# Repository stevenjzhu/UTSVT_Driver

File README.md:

# UTSVT_Driver
This is a PCB board to interface the motors and various components through CAN bus for UTSVT

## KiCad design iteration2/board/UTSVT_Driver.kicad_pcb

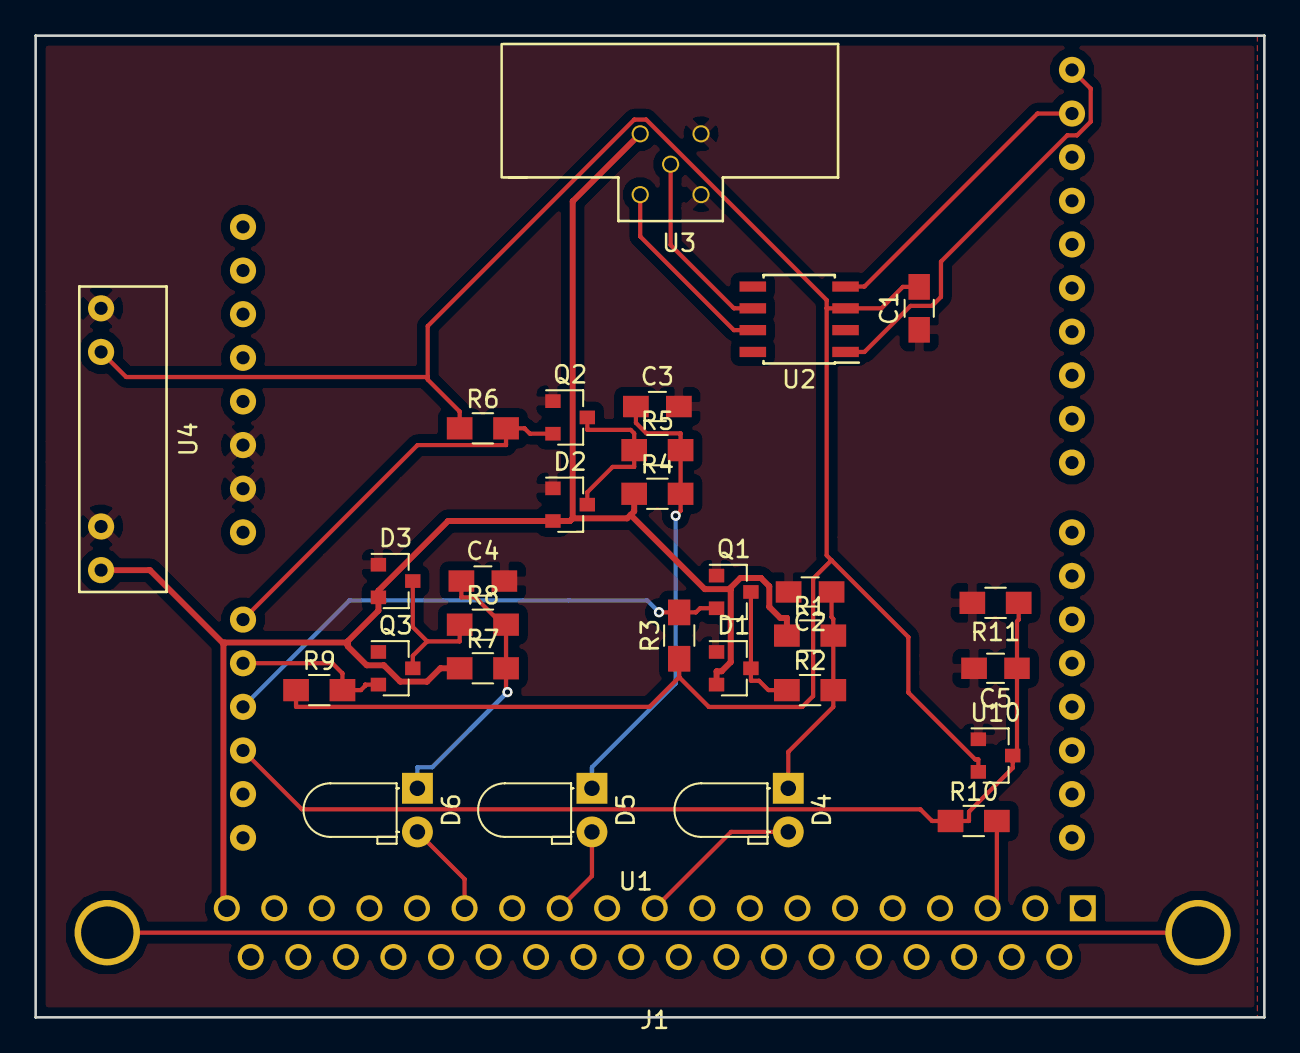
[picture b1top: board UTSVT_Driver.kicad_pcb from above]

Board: 2 copper layers, 71.5 x 57.1 mm, 31 parts (0 on the bottom side), 21 nets.

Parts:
C1: C; C_0805_HandSoldering
C2, C3, C4, C5: 100nF; C_0805_HandSoldering
D1, D2, D3: BAV99; SOT-23
D4, D5, D6: LED; LED_D3.0mm_Horizontal_O1.27mm_Z10.0mm
J1: DB37_Female_MountingHoles; DB37FC
Q1, Q2, Q3: 2N7002; SOT-23
R1, R2, R3, R4, R5, R6, R7, R8, R9, R10: 10K; R_0805_HandSoldering
R11: 1M; R_0805_HandSoldering
U1: Nucleo; AFBShieldBoard
U2: SN65HVD230; SOIC-8_3.9x4.9mm_Pitch1.27mm
U3: CAN_adapter
U4: REM1_12to3.3
U10: BAV99; SOT-23

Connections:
3.3V: C1.2, R3.1, R6.1, R9.1, U2.3, U4.3, U10.2
+12V: D1.2, D2.2, D3.2, J1.19, R1.1, R4.1, R7.1, U3.2, U4.1
/step_down_circuit1/Vin: C2.1, D4.1, R1.2, R2.2
/step_down_circuit1/Vout: Q1.2, R3.2, U1.11
/step_down_circuit2/Vin: C3.1, D5.1, R4.2, R5.2
/step_down_circuit2/Vout: Q2.2, R6.2, U1.9
/step_down_circuit3/Vin: C4.1, D6.1, R7.2, R8.2
/step_down_circuit3/Vout: Q3.2, R9.2, U1.10
/step_down_circuit_analog1/Vin: J1.3, R10.2
/step_down_circuit_analog1/Vout: C5.1, R10.1, R11.1, U1.12, U10.3
GND: C1.1, C2.2, C3.2, C4.2, C5.2, D1.1, D2.1, D3.1, Q1.1, Q2.1, Q3.1, R11.2, U1.6, U1.7, U2.2, U3.1, U3.3, U4.2, U4.4, U10.1
unnamed: D1.3, Q1.3, R2.1
unnamed: D2.3, Q2.3, R5.1
unnamed: D3.3, Q3.3, R8.1
unnamed: D4.2, J1.10
unnamed: D5.2, J1.12
unnamed: D6.2, J1.14
unnamed: U1.15, U2.1
unnamed: U1.16, U2.4
unnamed: U2.6, U3.5
unnamed: U2.7, U3.4

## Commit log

2017-10-12 ADD README.md
2017-10-12 Populate README.md
2017-10-12 Added .gitignore
2017-10-12 Reorganized repo
2017-10-21 Organized library
2017-10-21 Renamed folders and removed extra files
2017-10-21 Removed sym files
2017-10-21 Organized into library and sheet
2017-10-21 Update PCB
    update pcb 10/21
2017-10-23 Changed PCB
    Updated UTSVT_Driver.kicad_pcb and created a footer for the headers so that it will line up with the microcontroller
2017-10-26 Added traces
2017-10-26 Modified to accept potentiometer input
2017-10-26 Update Netlist
2017-10-26 Redo netlist
2017-10-26 finish wiring
2017-10-26 Generated netlist
2017-10-27 Redid some components to fit footprint
2017-11-04 partially resolved merge issues and added script for automatic merging
2017-11-04 I want this gone so i can merge
